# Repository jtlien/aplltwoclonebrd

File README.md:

# aplltwoclonebrd
An apple II clone board in kicad 
I needed a good source of documentation for the Apple II clone board that I had bought back in the early 1980s.   It wat in my closet for about 40 years and I recently wanted to get it out to get it to work and could not find a good source of documentation in an up to date CAD system.   So I made this design which represents to the best of my knowledge the original apple 2 clone board that I had.
As of Fall/2021, I have a fairly complete schemtic, chip layout and the start of a routed board in KICAD.    This may also be convenient for people building or working on vintage apple II hardware to use some of the nice KICAD tools like iBom to populate their boards etc.    Plus the design rule checkers should they get to the point of building a board.   My own plans are possibly to build a four layer board, with only a +5 Volt supply (-5v can be generated by a buck converter chip).
+12 and -12 Volts were needed for old serial ports and are not used much anymore.

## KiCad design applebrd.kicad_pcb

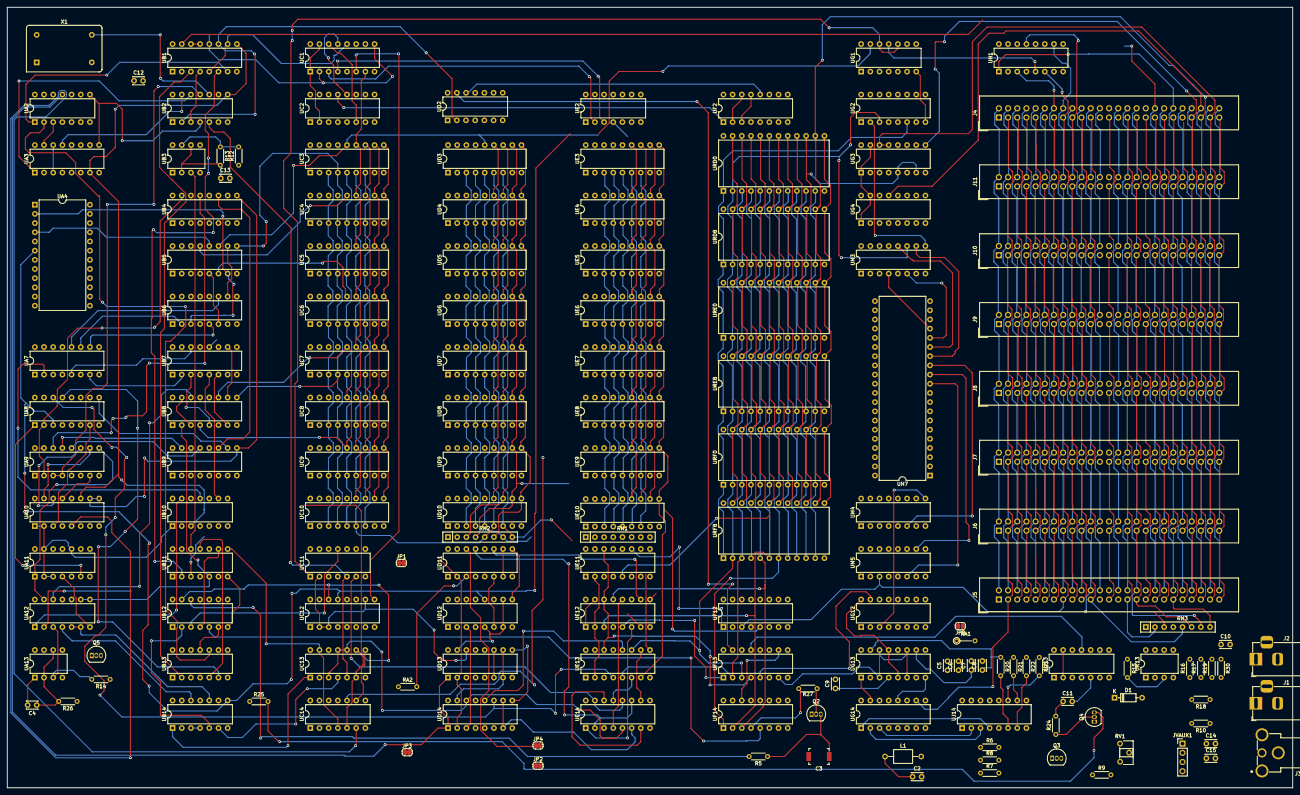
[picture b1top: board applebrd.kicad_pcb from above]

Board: 4 copper layers, 355.6 x 215.9 mm, 156 parts (0 on the bottom side), 322 nets.

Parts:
C2: 47pF; C_Disc_D3.0mm_W2.0mm_P2.50mm
C3: 3-50pF; C_Trimmer_Murata_TZW4
C4, C9, C11, C12, C13, C14, C15: .1uF; C_Disc_D3.0mm_W2.0mm_P2.50mm
C5, C6, C7, C8: .022uF; C_Disc_D3.0mm_W2.0mm_P2.50mm
C10: .1 uF; C_Disc_D3.0mm_W2.0mm_P2.50mm
D1: 1N914; D_DO-35_SOD27_P7.62mm_Horizontal
J1, J2: Jack-DC; BarrelJack_Horizontal
J3: RCJ-014; CUI_RCJ-014
J4, J5, J6, J7, J8, J9, J10, J11: Conn_02x25_Counter_Clockwise_Shielded; IDC-Header_2x25_P2.54mm_Vertical
JP1, JP3: SolderJumper_2_Bridged; SolderJumper-2_P1.3mm_Bridged_RoundedPad1.0x1.5mm
JP2, JP4, JP9: SolderJumper_2_Open; SolderJumper-2_P1.3mm_Open_RoundedPad1.0x1.5mm
JVAUX1: Conn_01x04; PinHeader_1x04_P2.54mm_Vertical
L1: 27uH; L_Axial_L5.0mm_D3.6mm_P10.00mm_Horizontal_Murata_BL01RN1A2A2
Q2, Q3, Q5: 2N3904; TO-92_Inline
Q4: Q_NPN_Darlington_EBC; TO-92_Inline
R5, R14: 1K; R_Axial_DIN0204_L3.6mm_D1.6mm_P5.08mm_Horizontal
R6: 2.7K; R_Axial_DIN0204_L3.6mm_D1.6mm_P5.08mm_Horizontal
R7: 1.5K; R_Axial_DIN0204_L3.6mm_D1.6mm_P5.08mm_Horizontal
R8: 2K; R_Axial_DIN0204_L3.6mm_D1.6mm_P5.08mm_Horizontal
R9: 10; R_Axial_DIN0204_L3.6mm_D1.6mm_P5.08mm_Horizontal
R10, R25: 27; R_Axial_DIN0204_L3.6mm_D1.6mm_P5.08mm_Horizontal
R12, R19, R30: 12K; R_Axial_DIN0204_L3.6mm_D1.6mm_P5.08mm_Horizontal
R13: 3.3M; R_Axial_DIN0204_L3.6mm_D1.6mm_P5.08mm_Horizontal
R15: 1Meg; R_Axial_DIN0204_L3.6mm_D1.6mm_P5.08mm_Horizontal
R16, R17: 12 K; R_Axial_DIN0204_L3.6mm_D1.6mm_P5.08mm_Horizontal
R18, R20, R21, R22, R23: 100; R_Axial_DIN0204_L3.6mm_D1.6mm_P5.08mm_Horizontal
R24: 47K; R_Axial_DIN0204_L3.6mm_D1.6mm_P5.08mm_Horizontal
R26: 2.2Meg; R_Axial_DIN0204_L3.6mm_D1.6mm_P5.08mm_Horizontal
R27: 4.7K; R_Axial_DIN0204_L3.6mm_D1.6mm_P5.08mm_Horizontal
RA1: 1K; R_Axial_DIN0204_L3.6mm_D1.6mm_P5.08mm_Vertical
RA2: 1K; R_Axial_DIN0204_L3.6mm_D1.6mm_P5.08mm_Horizontal
RN1, RN2: R_Network07_US; R_Array_SIP8
RN3: R_Network07x1k; R_Array_SIP8
RV1: 200; Potentiometer_ACP_CA6-H2,5_Horizontal
UA2: 74LS00; DIP-14_W7.62mm
UA3: 74LS166; DIP-16_W7.62mm
UA4: 2716; DIP-24_W15.24mm
UA7: AKBD; DIP-16_W7.62mm
UA8: 74LS257; DIP-16_W7.62mm
UA9: 74LS151; DIP-16_W7.62mm
UA10: 74LS194; DIP-16_W7.62mm
UA11: 74LS74; DIP-14_W7.62mm
UA12: 74LS02; DIP-14_W7.62mm
UA13: LM555xMM; DIP-8_W7.62mm
UB1: 74LS175; DIP-16_W7.62mm
UB2: 74LS86; DIP-14_W7.62mm
UB3: LM555xMM; DIP-8_W7.62mm
UB4, UB9: 74LS194; DIP-16_W7.62mm
UB5, UB8: 74LS174; DIP-16_W7.62mm
UB6, UB7: 74LS257; DIP-16_W7.62mm
UB10: 74LS74; DIP-14_W7.62mm
UB11: 74LS08; DIP-14_W7.62mm
UB12: 74LS11; DIP-14_W7.62mm
UB13, UB14: 74LS02; DIP-14_W7.62mm
UC1: 74LS153; DIP-16_W7.62mm
UC2: 74LS195; DIP-16_W7.62mm
UC3, UC4, UC5, UC6, UC7, UC8, UC9, UC10: 2116; DIP-18_W7.62mm
UC11: 74LS04; DIP-14_W7.62mm
UC12: 74LS257; DIP-16_W7.62mm
UC13: 74LS51; DIP-14_W7.62mm
UC14: 74LS32; DIP-14_W7.62mm
UD2: 74LS20; DIP-14_W7.62mm
UD3, UD4, UD5, UD6, UD7, UD8, UD9, UD10: 2116; DIP-18_W7.62mm
UD11, UD12, UD13, UD14: 74LS161; DIP-16_W7.62mm
UE2: 74LS02; DIP-14_W7.62mm
UE3, UE4, UE5, UE6, UE7, UE8, UE9, UE10: 2116; DIP-18_W7.62mm
UE11, UE12, UE13: 74LS153; DIP-16_W7.62mm
UE14: 74LS283; DIP-16_W7.62mm
UF2: 74LS139; DIP-16_W7.62mm
UF12, UF13: 74LS138; DIP-16_W7.62mm
UF14: 74LS259; DIP-16_W7.62mm
UG1: 74LS08; DIP-14_W7.62mm
UG2, UG12: 74LS138; DIP-16_W7.62mm
UG3, UG4: 8T28; DIP-16_W7.62mm
UG13: NE558; DIP-16_W7.62mm
UG14: 74LS251; DIP-16_W7.62mm
UH1: 74LS257; DIP-16_W7.62mm
UH7: WD65C02; DIP-40_W15.24mm
UJ13: 74LS74; DIP-14_W7.62mm
UJ14: GAMECNTL; DIP-16_W7.62mm
UK13: LM741; DIP-8_W7.62mm
UM3, UM4, UM5: 74LS367; DIP-16_W7.62mm
URD0, URD8: 2716; DIP-24_W15.24mm
URE0, URE8: 2716; DIP-24_W15.24mm
URF0, URF8: 2716; DIP-24_W15.24mm
X1: CXO_DIP14; Oscillator_DIP-14

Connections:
+5V: J4.25, J5.25, J6.25, J7.25, J8.25, J9.25, J10.25, J11.25, R9.1, R12.1, R26.1, RA1.1, RA2.1, RN1.1, RN3.1, UA2.14, UA3.16, UA4.24, UA7.1, UA8.16, UA9.16, UA10.16, UA11.14, UA12.14, UA13.4, UA13.8, UB1.16, UB2.14, UB3.4, UB3.8, UB4.16, UB5.16, UB6.16, UB7.16, UB8.16, UB9.16, UB10.14, UB11.14, UB12.14, UB13.14, UB14.14, UC1.16, UC2.16, UC3.16, UC4.16, UC5.16, UC6.16, UC7.16, UC8.16, UC9.16, UC10.16, UC11.14, UC12.16, UC13.14, UC14.14, UD2.14, UD3.16, UD4.16, UD5.16, UD6.16, UD7.16, UD8.16, UD9.16, UD10.16, UD11.16, UD12.16, UD13.16, UD14.16, UE2.14, UE3.16, UE4.16, UE5.16, UE6.16, UE7.16, UE8.16, UE9.16, UE10.16, UE11.16, UE12.16, UE13.16, UE14.16, UF12.16, UF13.16, UF14.16, UG1.14, UG2.16, UG3.16, UG4.16, UG12.16, UG13.5, UG13.13, UG14.16, UJ13.14, UJ14.1, UK13.7, UM3.16, UM4.16, UM5.16, URD0.24, URD8.24, URE0.24, URE8.24, URF0.24, URF8.24, X1.1, X1.14
+12V: C14.1, J4.50, J5.50, J6.50, J7.50, J8.50, J9.50, J10.50, J11.50, JVAUX1.1
-5V: C15.1, J4.34, J5.34, J6.34, J7.34, J8.34, J9.34, J10.34, JVAUX1.2, UK13.4
-12V: J4.33, J5.33, J6.33, J7.33, J8.33, J9.33, J10.33
/7M: J4.36, J5.36, J6.36, J7.36, J8.36, J9.36, J10.36, J11.36, UB1.15, UB2.1, UB12.9
/14M: UA3.7, UA10.9, UA10.10, UA10.11, UB1.9, UB2.8, UB4.9, UB9.9, UB10.3, UB12.8, UC2.10
/A0: J4.2, J5.2, J6.2, J7.2, J8.2, J9.2, J10.2, J11.2, UE13.3, UF14.13, UG14.11, UM5.11, URD0.8, URD8.8, URE0.8, URE8.8, URF0.8, URF8.8
/A1: J4.3, J5.3, J6.3, J7.3, J8.3, J9.3, J10.3, J11.3, UE13.13, UF14.1, UG14.10, UM4.5, URD0.7, URD8.7, URE0.7, URE8.7, URF0.7, URF8.7
/A2: J4.4, J5.4, J6.4, J7.4, J8.4, J9.4, J10.4, J11.4, UE12.3, UF14.2, UG14.9, UM5.7, URD0.6, URD8.6, URE0.6, URE8.6, URF0.6, URF8.6
/A3: J4.5, J5.5, J6.5, J7.5, J8.5, J9.5, J10.5, J11.5, UE12.13, UF14.3, UM5.9, URD0.5, URD8.5, URE0.5, URE8.5, URF0.5, URF8.5
/A4: J4.6, J5.6, J6.6, J7.6, J8.6, J9.6, J10.6, J11.6, UE12.5, UF13.1, UG2.1, UM4.7, URD0.4, URD8.4, URE0.4, URE8.4, URF0.4, URF8.4
/A5: J4.7, J5.7, J6.7, J7.7, J8.7, J9.7, J10.7, J11.7, UE13.5, UF13.2, UG2.2, UM3.9, URD0.3, URD8.3, URE0.3, URE8.3, URF0.3, URF8.3
/A6: J4.8, J5.8, J6.8, J7.8, J8.8, J9.8, J10.8, J11.8, UE13.11, UF13.3, UG2.3, UM3.11, URD0.2, URD8.2, URE0.2, URE8.2, URF0.2, URF8.2
/A7: J4.9, J5.9, J6.9, J7.9, J8.9, J9.9, J10.9, J11.9, UE11.3, UF13.6, UG2.6, UM3.7, URD0.1, URD8.1, URE0.1, URE8.1, URF0.1, URF8.1
/A8: J4.10, J5.10, J6.10, J7.10, J8.10, J9.10, J10.10, J11.10, UE11.13, UG12.1, UM3.5, URD0.23, URD8.23, URE0.23, URE8.23, URF0.23, URF8.23
/A9: J4.11, J5.11, J6.11, J7.11, J8.11, J9.11, J10.11, J11.11, UE12.11, UG12.2, UM3.3, URD0.22, URD8.22, URE0.22, URE8.22, URF0.22, URF8.22
/A10: J4.12, J5.12, J6.12, J7.12, J8.12, J9.12, J10.12, J11.12, UE11.5, UG12.3, UM4.9, URD0.19, URD8.19, URE0.19, URE8.19, URF0.19, URF8.19
/A11: J4.13, J5.13, J6.13, J7.13, J8.13, J9.13, J10.13, J11.13, UE11.11, UF12.1, UM4.11
/A12: J4.14, J5.14, J6.14, J7.14, J8.14, J9.14, J10.14, J11.14, UC1.3, UE2.2, UF12.2, UH1.3, UM4.3
/A12-13: UA9.9, UA11.1, UA12.13
/A13: J4.15, J5.15, J6.15, J7.15, J8.15, J9.15, J10.15, J11.15, UC1.4, UE2.3, UF12.3, UH1.6, UM5.3
/A14: J4.16, J5.16, J6.16, J7.16, J8.16, J9.16, J10.16, J11.16, UG1.4, UH1.10, UM5.13
/A15: J4.17, J5.17, J6.17, J7.17, J8.17, J9.17, J10.17, J11.17, UG1.5, UH1.13, UM4.13
/AD0: UH7.9, UM5.12
/AD1: UH7.10, UM4.4
/AD2: UH7.11, UM5.6
/AD3: UH7.12, UM5.10
/AD4: UH7.13, UM4.6
/AD5: UH7.14, UM3.10
/AD6: UH7.15, UM3.12
/AD7: UH7.16, UM3.6
/AD8: UH7.17, UM3.4
/AD9: UH7.18, UM3.2
/AD10: UH7.19, UM4.10
/AD11: UH7.20, UM4.12
/AD12: UH7.22, UM4.2
/AD13: UH7.23, UM5.2
/AD14: UH7.24, UM5.14
/AD15: UH7.25, UM4.14
/AN0: UF14.9, UJ14.15
/AN1: UF14.10, UJ14.14
/AN2: UF14.11, UJ14.13
/AN3: UF14.12, UJ14.12
/AX: UB13.9, UC1.14, UC2.4, UC2.6, UC2.14, UE11.2, UE12.2, UE13.2
/CASSETTE_OUT: UF13.13, UJ13.11
/CREF: UB1.3, UB13.2
/D0: J4.49, J5.49, J6.49, J7.49, J8.49, J9.49, J10.49, J11.49, UG4.2, UG4.4, URD0.9, URD8.9, URE0.9, URE8.9, URF0.9, URF8.9
/D1: J4.48, J5.48, J6.48, J7.48, J8.48, J9.48, J10.48, J11.48, UG3.2, UG3.4, URD0.10, URD8.10, URE0.10, URE8.10, URF0.10, URF8.10
/D2: J4.47, J5.47, J6.47, J7.47, J8.47, J9.47, J10.47, J11.47, UG3.13, UG3.14, URD0.11, URD8.11, URE0.11, URE8.11, URF0.11, URF8.11
/D3: J4.46, J5.46, J6.46, J7.46, J8.46, J9.46, J10.46, J11.46, UG4.13, UG4.14, URD0.13, URD8.13, URE0.13, URE8.13, URF0.13, URF8.13
/D4: J4.45, J5.45, J6.45, J7.45, J8.45, J9.45, J10.45, J11.45, UG4.5, UG4.7, URD0.14, URD8.14, URE0.14, URE8.14, URF0.14, URF8.14
/D5: J4.44, J5.44, J6.44, J7.44, J8.44, J9.44, J10.44, J11.44, UG3.5, UG3.7, URD0.15, URD8.15, URE0.15, URE8.15, URF0.15, URF8.15
/D6: J4.43, J5.43, J6.43, J7.43, J8.43, J9.43, J10.43, J11.43, UG3.9, UG3.11, URD0.16, URD8.16, URE0.16, URE8.16, URF0.16, URF8.16
/D7: J4.42, J5.42, J6.42, J7.42, J8.42, J9.42, J10.42, J11.42, UA8.13, UG4.9, UG4.11, UG14.5, URD0.17, URD8.17, URE0.17, URE8.17, URF0.17, URF8.17
/DB0: UB6.9, UG4.3, UH7.33
/DB1: UB6.12, UG3.3, UH7.32
/DB2: UB6.7, UH7.31
/DB3: UB6.4, UH7.30
/DB4: UB7.9, UG4.6, UH7.29
/DB5: UB7.12, UG3.6, UH7.28
/DB6: UB7.4, UG3.10, UH7.27
/DB7: UB7.7, UG4.10, UH7.26
/DEV_SEL_0: J4.41, UG2.15
/DEV_SEL_1: J5.41, UG2.14
/DEV_SEL_2: J6.41, UG2.13
/DEV_SEL_3: J7.41, UG2.12
/DEV_SEL_4: J8.41, UG2.11
/DEV_SEL_5: J9.41, UG2.10
/DEV_SEL_6: J10.41, UG2.9
/DEV_SEL_7: J11.41, UG2.7
/DMAIN1: J4.24, J5.27
/DMAIN2: J5.24, J6.27
/DMAIN3: J6.24, J7.27
/DMAIN4: J7.24, J8.27
/DMAIN5: J8.24, J9.27
/DMAIN6: J9.24, J10.27
/DMAIN7: J10.24, J11.27
/F13_7: UF13.7, UG13.3, UG13.6, UG13.11, UG13.14
/GRAPHICS_TXT: R27.2, UB13.12, UF14.4
/H0: UA8.14, UC13.10, UC13.11, UD14.14, UE13.4
/H1: UB13.3, UD14.13, UE13.12
/H2: UD14.12, UE12.4
/H3: UB12.2, UC13.3, UD14.11, UE14.5
/H4: UB14.5, UC13.2, UD13.14, UE14.3
/H5: UB14.6, UC11.5, UC13.4, UC13.5, UD13.13
/HBL: UB12.13, UC12.14, UC13.6, UC13.9, UC14.5
/HIRES: UB11.6, UC11.1, UC12.5, UG1.10, UG1.12
/INTIN1: J4.23, J5.28
/INTIN2: J5.23, J6.28
/INTIN3: J6.23, J7.28
/INTIN4: J7.23, J8.28
/INTIN5: J8.23, J9.28
/INTIN6: J9.23, J10.28
/INTIN7: J10.23, J11.28
/IO_SEL_1: J4.18, J5.1, J5.18, J6.18, J7.18, J8.18, J9.18, J10.18, J11.18, UA2.4, UG12.14
/IO_SEL_2: J6.1, UG12.13
/IO_SEL_3: J7.1, UG12.12
/IO_SEL_4: J8.1, UG12.11
/IO_SEL_5: J9.1, UG12.10
/IO_SEL_6: J10.1, UG12.9
/IO_SEL_7: J11.1, UG12.7
/K6: UA7.7, UB7.2
/KB0: UA7.12, UB6.11
/KB1: UA7.13, UB6.14
/KB2: UA7.10, UB6.5
/KB3: UA7.11, UB6.2
/KB4: UA7.6, UB7.11
/KB5: UA7.5, UB7.14
/KB7: UB7.5, UB10.9
/LORES_HIRES: UB11.4, UF14.7
/MIX_MODE: UB12.5, UF14.5
/P0: J4.38, J4.40, J5.38, J5.40, J6.38, J6.40, J7.38, J7.40, J8.38, J8.40, J9.38, J9.40, J10.38, J10.40, J11.38, J11.40, UA2.1, UB1.6, UB1.7, UB11.2, UB12.10, UD2.5, UE11.14, UE12.14, UE13.14, UF12.4, UF13.4, UG2.5, UH1.1
/Q3: J4.37, J5.37, J6.37, J7.37, J8.37, J9.37, J10.37, J11.37, UC1.13, UC2.9, UC2.12
/R5: C2.1, C3.1, L1.1, Q2.3, R5.1, R6.2
/RA0: RN1.7, RN2.6, UC3.10, UC4.10, UC5.10, UC6.10, UC7.10, UC8.10, UC9.10, UC10.10, UD3.10, UD4.10, UD5.10, UD6.10, UD7.10, UD8.10, UD9.10, UD10.10, UE3.10, UE4.10, UE5.10, UE6.10, UE7.10, UE8.10, UE9.10, UE10.10, UE13.7
/RA1: RN1.5, RN2.4, UC3.11, UC4.11, UC5.11, UC6.11, UC7.11, UC8.11, UC9.11, UC10.11, UD3.11, UD4.11, UD5.11, UD6.11, UD7.11, UD8.11, UD9.11, UD10.11, UE3.11, UE4.11, UE5.11, UE6.11, UE7.11, UE8.11, UE9.11, UE10.11, UE12.7
/RA2: RN1.3, RN2.3, UC3.12, UC4.12, UC5.12, UC6.12, UC7.12, UC8.12, UC9.12, UC10.12, UD3.12, UD4.12, UD5.12, UD6.12, UD7.12, UD8.12, UD9.12, UD10.12, UE3.12, UE4.12, UE5.12, UE6.12, UE7.12, UE8.12, UE9.12, UE10.12, UE11.7
/RA3: RN1.8, RN2.8, UC3.7, UC4.7, UC5.7, UC6.7, UC7.7, UC8.7, UC9.7, UC10.7, UD3.7, UD4.7, UD5.7, UD6.7, UD7.7, UD8.7, UD9.7, UD10.7, UE3.7, UE4.7, UE5.7, UE6.7, UE7.7, UE8.7, UE9.7, UE10.7, UE13.9
/RA4: RN1.6, RN2.5, UC3.6, UC4.6, UC5.6, UC6.6, UC7.6, UC8.6, UC9.6, UC10.6, UD3.6, UD4.6, UD5.6, UD6.6, UD7.6, UD8.6, UD9.6, UD10.6, UE3.6, UE4.6, UE5.6, UE6.6, UE7.6, UE8.6, UE9.6, UE10.6, UE12.9
/RA5: RN1.4, RN2.7, UC3.5, UC4.5, UC5.5, UC6.5, UC7.5, UC8.5, UC9.5, UC10.5, UD3.5, UD4.5, UD5.5, UD6.5, UD7.5, UD8.5, UD9.5, UD10.5, UE3.5, UE4.5, UE5.5, UE6.5, UE7.5, UE8.5, UE9.5, UE10.5, UE11.9
/RA6: UC1.7, UC3.13, UC4.13, UC5.13, UC6.13, UC7.13, UC8.13, UC9.13, UC10.13, UD3.13, UD4.13, UD5.13, UD6.13, UD7.13, UD8.13, UD9.13, UD10.13, UE3.13, UE4.13, UE5.13, UE6.13, UE7.13, UE8.13, UE9.13, UE10.13
/RAM_SEL: UA2.6, UB6.15, UB7.15
/RDL0: UA4.5, UB5.10, UB6.10
/RDL1: UA4.4, UB5.12, UB6.13
/RDL2: UA4.3, UB5.5, UB6.6
/RDL3: UA4.2, UB5.7, UB6.3
/RDL4: UA4.1, UB7.10, UB8.10
/RDL5: UA4.23, UB7.13, UB8.12
/RDL6: UB7.3, UB8.5, UB11.13
/RDL7: UB7.6, UB8.7, UB13.6
/RDO0: UB5.11, UC3.14, UD3.14, UE3.14
/RDO1: UB5.13, UC4.14, UD4.14, UE4.14
/RDO2: UB5.4, UC5.14, UD5.14, UE5.14
/RDO3: UB5.6, UC6.14, UD6.14, UE6.14
/RDO4: UB8.11, UC7.14, UD7.14, UE7.14
/RDO5: UB8.13, UC8.14, UD8.14, UE8.14
/RDO6: UB8.4, UC9.14, UD9.14, UE9.14
/RDO7: UB8.6, UC10.14, UD10.14, UE10.14
/RDY: J4.21, J5.21, J6.21, J7.21, J8.21, J9.21, J10.21, J11.21, RN3.5, UH7.2
/RD_KBD: UB6.1, UB7.1, UD2.13, UF13.15
/RST_KBD_STROBE: UC11.3, UF13.14
/RW: UC3.3, UC14.9, UD3.3, UE3.3, UM5.5
/SERIAL_IN: UF13.9, UG14.7
/SOFT5_11: UA2.11, UD11.1, UD12.1, UD13.1, UD13.5, UD14.1, UD14.7, UD14.10, UE14.6
/SOFT-5: UA2.8, UA3.9, UA10.1, UA10.2, UA11.2, UA11.3, UA11.10, UA11.13, UB2.4, UB5.1, UB8.1, UB10.1, UB10.4, UC2.1, UF13.12, UF14.15, UJ13.3, UJ13.4
/STROBE: UF13.11, UJ14.5
/SYNC: R8.2, UC13.8
/SYSCLK: UB2.10, X1.8
/USER1: J4.39, J5.39, J6.39, J7.39, J8.39, J9.39, J10.39, J11.39, JP9.1, RN3.8
/V0: UA4.6, UA8.3, UB14.8, UB14.9, UC12.13, UD12.12, UD12.13, UE11.4, UG1.13
/V1: JP2.1, UA4.7, UC12.6, UD12.11, UD12.14, UE11.12
/V2: JP1.1, UB12.3, UC11.11, UD11.14, UE12.10
/V3: UB11.9, UD11.13, UE14.7, UE14.14
/V4: UB11.10, UB12.4, UD11.12, UE14.2, UE14.11
/V5: JP4.1, UD11.11
/VA: UA4.8, UC11.2, UC12.2, UC12.3, UC12.10, UD13.6, UD13.11
/~7M: UA3.6, UA8.10, UB1.13, UB1.14
/~CAS: UB13.8, UC2.13, UF2.1
/~CREF: UB1.2, UB2.2, UD2.2
/~DMA: J4.22, J5.22, J6.22, J7.22, J8.22, J9.22, J10.22, J11.22, RN3.3, UB11.1, UC11.13
/~HPE: UB2.5, UD13.9, UD13.12, UD14.9
/~INH: J4.32, J5.32, J6.32, J7.32, J8.32, J9.32, J10.32, RN3.7, UE2.5, URD0.18, URD8.18, URE0.18, URE8.18, URF0.18, URF8.18
/~IOENBBL: UF12.15, UG12.4, UG12.5
/~IO_STROBE: J4.20, J5.20, J6.20, J7.20, J8.20, J9.20, J10.20, J11.20, UF12.14
/~IRQ: J4.30, J5.30, J6.30, J7.30, J8.30, J9.30, J10.30, RN3.4, UH7.4
/~LDPS: UA2.3, UA3.15, UD11.2, UD12.2, UD13.2, UD14.2
/~NMI: J4.29, J5.29, J6.29, J7.29, J8.29, J9.29, J10.29, RN3.2, UH7.6
/~RAS: UC2.7, UC2.15
/~RES: J4.31, J5.31, J6.31, J7.31, J8.31, J9.31, J10.31, Q5.3, RN3.6, UA7.3, UH7.40
GND: C2.2, C3.2, C4.2, C5.2, C6.2, C7.2, C8.2, C9.2, C12.2, C13.2, C14.2, C15.2, D1.2, J1.1, J2.1, J3.1A, J3.1B, J3.1C, J4.26, J5.26, J6.26, J7.26, J8.26, J9.26, J10.26, J11.26, JVAUX1.4, L1.2, Q2.1, Q4.1, Q5.1, R16.2, R17.2, R18.2, RN2.1, RV1.3, UA2.7, UA2.9, UA2.10, UA2.12, UA2.13, UA3.8, UA4.12, UA4.18, UA4.19, UA4.20, UA4.21, UA4.22, UA7.8, UA8.8, UA8.15, UA9.8, UA10.8, UA11.4, UA12.7, UA13.1, UB1.8, UB2.7, UB2.9, UB3.1, UB4.8, UB5.8, UB6.8, UB7.8, UB8.8, UB9.8, UB10.7, UB11.7, UB12.7, UB13.7, UB14.7, UC1.1, UC1.8, UC1.15, UC2.2, UC2.3, UC2.8, UC3.8, UC4.8, UC5.8, UC6.8, UC7.8, UC8.8, UC9.8, UC10.8, UC11.7, UC11.8, UC12.8, UC12.11, UC12.15, UC13.7, UC14.7, UD2.7, UD3.8, UD4.8, UD5.8, UD6.8, UD7.8, UD8.8, UD9.8, UD10.8, UD11.6, UD11.8, UD12.3, UD12.4, UD12.6, UD12.8, UD13.3, UD13.4, UD13.8, UD14.3, UD14.4, UD14.5, UD14.6, UD14.8, UE2.7, UE3.8, UE4.8, UE5.8, UE6.8, UE7.8, UE8.8, UE9.8, UE10.8, UE11.1, UE11.8, UE11.15, UE12.1, UE12.8, UE12.15, UE13.1, UE13.8, UE13.15, UE14.8, UF2.8, UF2.15, UF12.8, UF13.8, UF14.8, UG1.7, UG2.8, UG3.8, UG4.8, UG12.8, UG13.12, UG14.8, UH1.8, UH1.14, UH1.15, UH7.1, UH7.21, UH7.38, UJ13.7, UJ14.8, UM3.8, UM4.8, UM5.8, URD0.12, URD8.12, URE0.12, URE8.12, URF0.12, URF8.12, X1.7
unnamed: C4.1, R26.2, UA13.2, UA13.6
unnamed: C5.1, R21.1, UG13.2
unnamed: C6.1, R22.1, UG13.7
unnamed: C7.1, R23.1, UG13.10
unnamed: C8.1, R20.1, UG13.15
unnamed: C9.1, UG13.4
unnamed: C10.1, R30.1
unnamed: C10.2, J2.2
unnamed: C11.1, D1.1, R24.2
unnamed: C11.2, UJ13.5
unnamed: C12.1, R25.1
unnamed: C13.1, R13.2, UB3.2, UB3.6
unnamed: J1.2, R18.1, R19.1
unnamed: J3.2, R10.1
unnamed: JP1.2, JP2.2, UB14.11
unnamed: JP3.1, UC11.10
unnamed: JP3.2, JP4.2, UB14.2
unnamed: RA2.2, UD11.3
unnamed: JP9.2, RA1.2, UG12.6
unnamed: JVAUX1.3, Q3.1, RV1.1
unnamed: Q2.2, R27.1
unnamed: Q3.2, R6.1, R7.1, R8.1
unnamed: Q3.3, R9.2
unnamed: Q4.2, R24.1
unnamed: Q4.3, R25.2
unnamed: Q5.2, R14.1
unnamed: R5.2, UB12.12
unnamed: R7.2, UB10.5
unnamed: R10.2, RV1.2
unnamed: R12.2, R13.1, UB3.7
unnamed: R14.2, UA12.3, UA13.3
unnamed: R15.1, UG14.4, UK13.6
unnamed: R15.2, R16.1, UK13.3
unnamed: R17.1, R30.2, UK13.2
unnamed: R19.2, UJ13.8, UJ13.12
unnamed: R20.2, UJ14.6
unnamed: R21.2, UJ14.10
unnamed: R22.2, UJ14.7
unnamed: R23.2, UJ14.11
unnamed: UA2.2, UB12.11, UB13.10, UD2.4
unnamed: UA2.5, UD2.8
unnamed: UA3.3, UA4.11
unnamed: UA3.4, UA4.17
unnamed: UA3.5, UA4.16
unnamed: UA3.10, UA4.15
unnamed: UA3.11, UA4.14
unnamed: UA3.12, UA4.13
unnamed: UA3.13, UB2.13
unnamed: UA3.14, UA4.10
unnamed: UA7.2, UB10.11
unnamed: UA8.2, UA9.2, UA9.15, UB4.15
unnamed: UA8.4, UB4.7
unnamed: UA8.9, UB4.10, UB9.10
unnamed: UA9.3, UA9.4, UB2.11
unnamed: UA9.5, UB10.2
unnamed: UA9.12, UB9.13
unnamed: UA9.13, UB9.15
unnamed: UA9.14, UB4.13
unnamed: UA8.7, UA10.3
unnamed: UA8.12, UA10.4
unnamed: UA10.5, UC14.6
unnamed: UA3.2, UA10.6, UB13.4
unnamed: UA3.1, UA10.12, UB2.12
unnamed: UA9.7, UA10.13
unnamed: UA9.11, UA10.14
unnamed: UA9.10, UA10.15
unnamed: UA8.1, UA11.6
unnamed: UA9.1, UA11.9
unnamed: UA11.11, UB9.1, UB9.2
unnamed: UA12.1, UB10.13
unnamed: UA12.2, UC11.4
unnamed: UA12.4, UB14.12
unnamed: UA12.5, UA12.6, UB14.10
unnamed: UA12.8, UA12.9, UB8.2, UB11.5
unnamed: UA12.10, UA12.11
unnamed: UA12.12, UB5.2, UB8.14
unnamed: UB1.4, UB2.3
unnamed: UB1.5, UB1.10, UC1.10, UC1.12
unnamed: UB1.12, UC1.2, UC1.9
unnamed: UB2.6, UD2.1
unnamed: UB4.1, UB4.2
unnamed: UB4.11, UB9.11
unnamed: UB5.9, UB8.9, UC3.4, UC4.4, UC5.4, UC6.4, UC7.4, UC8.4, UC9.4, UC10.4, UD3.4, UD4.4, UD5.4, UD6.4, UD7.4, UD8.4, UD9.4, UD10.4, UE3.4, UE4.4, UE5.4, UE6.4, UE7.4, UE8.4, UE9.4, UE10.4
unnamed: UB8.3, UB8.15
unnamed: UB10.10, UB10.12
unnamed: UB11.3, UH7.37
unnamed: UB11.8, UC13.13, UC14.4
unnamed: UB11.11, UB13.5
unnamed: UB3.3, UB11.12
unnamed: UB12.1, UB13.1
unnamed: UB12.6, UB13.11
unnamed: UB5.3, UB13.13
unnamed: UB14.1, UC13.1
unnamed: UB14.3, UB14.4
unnamed: UB14.13, UC13.12
unnamed: UC1.5, UC12.12
unnamed: UC1.6, UC12.9
unnamed: UC1.11, UC2.11
unnamed: UC2.5, UD2.6
unnamed: UC4.2, UD4.2, UE4.2
unnamed: UC4.3, UD4.3, UE4.3
unnamed: UC5.2, UD5.2, UE5.2
unnamed: UC5.3, UD5.3, UE5.3
unnamed: UC6.2, UD6.2, UE6.2
unnamed: UC7.2, UD7.2, UE7.2
unnamed: UC8.2, UD8.2, UE8.2
unnamed: UC9.2, UD9.2, UE9.2
unnamed: UC10.2, UD10.2, UE10.2
unnamed: UC3.2, UC6.3, UC7.3, UC8.3, UC10.3, UD3.2, UD6.3, UD7.3, UD8.3, UD9.3, UD10.3, UE3.2, UE6.3, UE7.3, UE8.3, UE9.3, UE10.3
unnamed: UC3.15, UC4.15, UC5.15, UC6.15, UC7.15, UC8.15, UC9.15, UC10.15, UF2.4
unnamed: UC11.6, UE14.12, UE14.15
unnamed: UC11.9, UD11.15
unnamed: UC11.12, UM3.1, UM3.15, UM4.1, UM4.15, UM5.1, UM5.15
unnamed: UC14.8, UG3.1, UG3.15, UG4.1, UG4.15
unnamed: UC14.10, UH7.3
unnamed: UD2.9, UF2.10, UG1.2
unnamed: UD2.10, UF2.11, UG1.1
unnamed: UD2.12, UF2.12
unnamed: UD3.15, UD4.15, UD5.15, UD6.15, UD7.15, UD8.15, UD9.15, UD10.15, UF2.5
unnamed: UD11.9, UD12.9
unnamed: UD11.4, UD11.5, UD11.7, UD11.10, UD12.15
unnamed: UD12.5, UD12.7, UD12.10, UD13.15
unnamed: UD13.7, UD13.10, UD14.15
unnamed: UE2.4, UF12.5
unnamed: UE3.15, UE4.15, UE5.15, UE6.15, UE7.15, UE10.15, UF2.6
unnamed: UE12.6, UE14.1
unnamed: UE12.12, UE14.4
unnamed: UE13.6, UE14.13
unnamed: UE13.10, UE14.10
unnamed: UF2.3, UF2.13, UH1.12
unnamed: UF2.2, UF2.14, UH1.9
unnamed: UF2.16, UH1.16
unnamed: UF12.6, UG1.6
unnamed: UF12.7, URD0.20, URD0.21
unnamed: UF12.9, URD8.20, URD8.21
unnamed: UF12.10, URE0.20, URE0.21
unnamed: UF12.11, URE8.20, URE8.21
unnamed: UF12.12, URF0.20, URF0.21
unnamed: UF12.13, URF8.20, URF8.21
unnamed: UF13.5, UG2.4, UG12.15
unnamed: UF13.10, UF14.14
unnamed: UG1.8, UH1.11
unnamed: UG1.11, UH1.5
unnamed: UG13.1, UG14.15
unnamed: UG13.8, UG14.12
unnamed: UG13.9, UG14.13
unnamed: UG13.16, UG14.14
unnamed: UG14.1, UJ14.4
unnamed: UG14.2, UJ14.3
unnamed: UG14.3, UJ14.2
unnamed: UH7.34, UM5.4
unnamed: UJ13.1, UJ13.2, UJ13.6, UJ13.10, UJ13.13

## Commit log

2021-10-10 Update allchippos.txt
    U3-U10 bad package type.
2021-10-10 Update README.md
    fix spelling error
2021-10-10 Add files via upload
    Ram chp wiring fixed.
2021-12-04 Fixed packages for ram chips from 18 to 16 pin
2022-01-16 Add files via upload
    Routed board gerbers.
